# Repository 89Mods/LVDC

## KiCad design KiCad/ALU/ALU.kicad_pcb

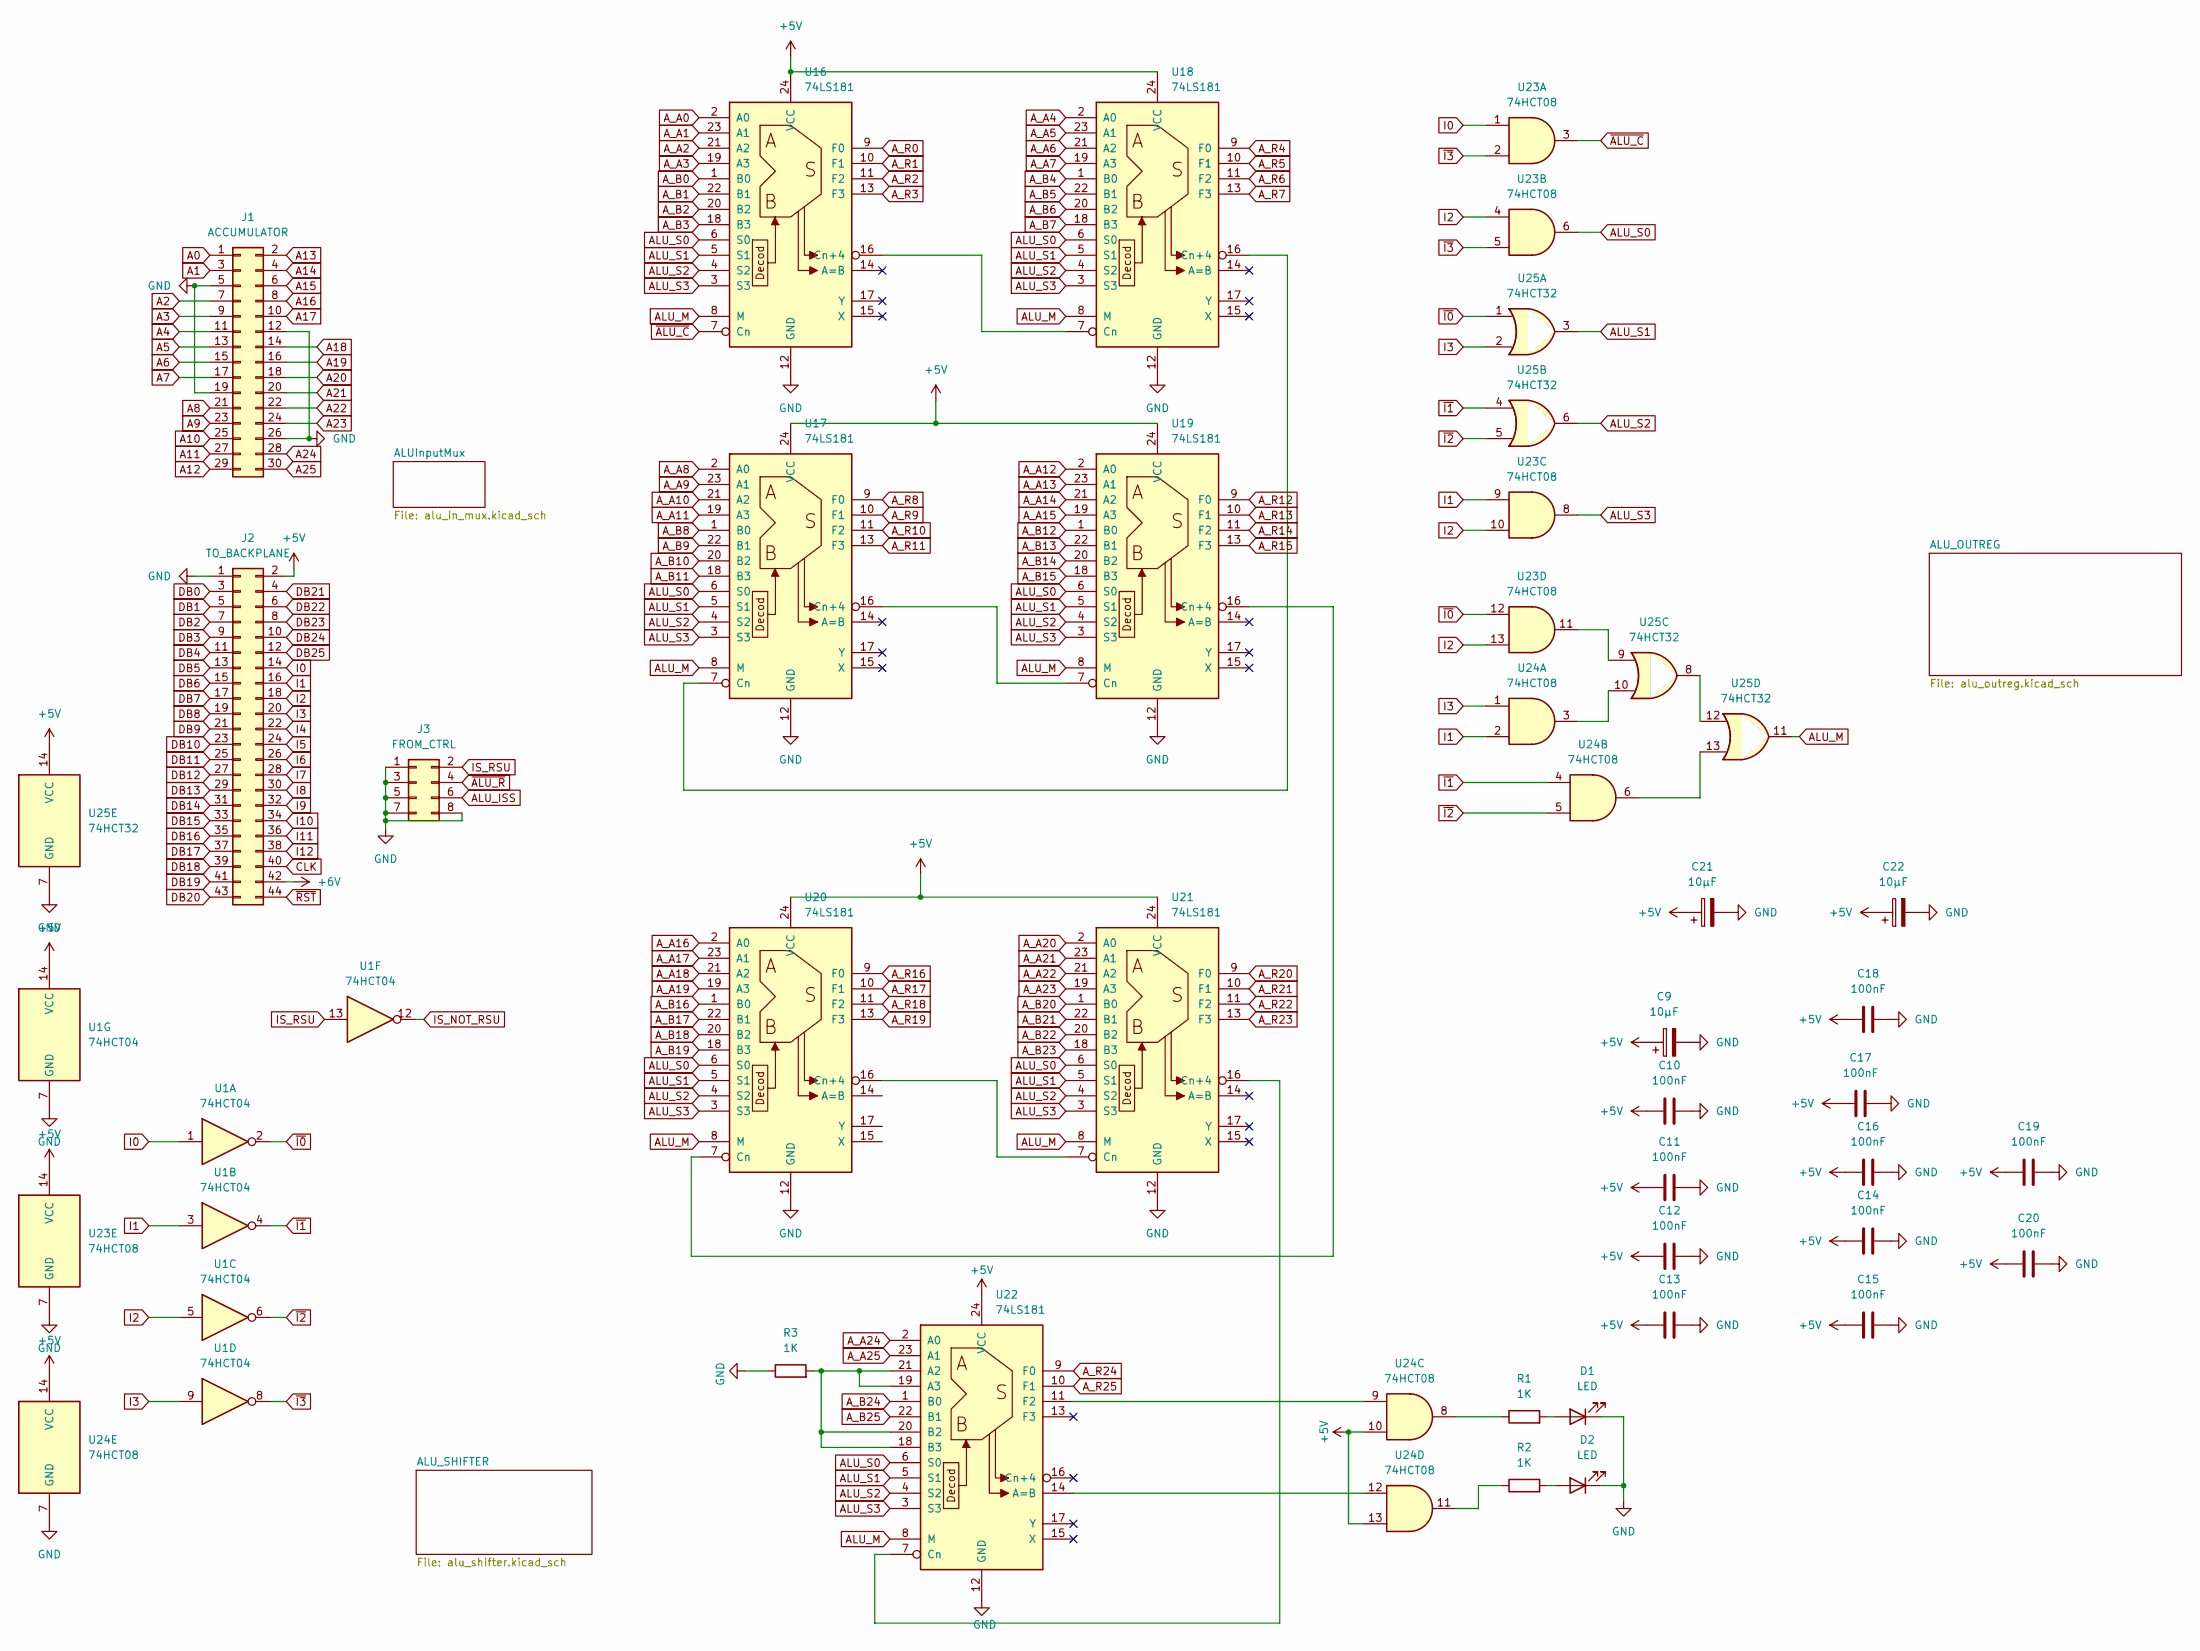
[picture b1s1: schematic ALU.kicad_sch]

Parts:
C9, C21, C22: 10µF; CP_Radial_D4.0mm_P2.00mm
C10, C11, C12, C13, C14, C15, C16, C17, C18, C19, C20: 100nF; C_0805_2012Metric_Pad1.18x1.45mm_HandSolder
D1, D2: LED; LED_1206_3216Metric_Pad1.42x1.75mm_HandSolder
J1: ACCUMULATOR; PinHeader_2x15_P2.54mm_Vertical
J2: TO_BACKPLANE; PinHeader_2x22_P2.54mm_Vertical
J3: FROM_CTRL; PinHeader_2x04_P2.54mm_Vertical
R1, R2, R3: 1K; R_1206_3216Metric_Pad1.30x1.75mm_HandSolder
U1: 74HCT04; SO-14_3.9x8.65mm_P1.27mm
U16, U17, U18, U19, U20, U21, U22: 74LS181; DIP-24_W15.24mm
U23, U24: 74HCT08; SO-14_3.9x8.65mm_P1.27mm
U25: 74HCT32; SO-14_3.9x8.65mm_P1.27mm

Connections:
+5V: C9.1, C10.1, C11.1, C12.1, C13.1, C14.1, C15.1, C16.1, C17.1, C18.1, C19.1, C20.1, C21.1, C22.1, J2.2, U1.14 (VCC), U16.24 (VCC), U17.24 (VCC), U18.24 (VCC), U19.24 (VCC), U20.24 (VCC), U21.24 (VCC), U22.24 (VCC), U23.14 (VCC), U24.10, U24.13, U24.14 (VCC), U25.14 (VCC); also elsewhere on the board
+6V: J2.42; also elsewhere on the board
A0: J1.1; also elsewhere on the board
A1: J1.3; also elsewhere on the board
A2: J1.7; also elsewhere on the board
A3: J1.9; also elsewhere on the board
A4: J1.11; also elsewhere on the board
A5: J1.13; also elsewhere on the board
A6: J1.15; also elsewhere on the board
A7: J1.17; also elsewhere on the board
A8: J1.21; also elsewhere on the board
A9: J1.23; also elsewhere on the board
A10: J1.25; also elsewhere on the board
A11: J1.27; also elsewhere on the board
A12: J1.29; also elsewhere on the board
A13: J1.2; also elsewhere on the board
A14: J1.4; also elsewhere on the board
A15: J1.6; also elsewhere on the board
A16: J1.8; also elsewhere on the board
A17: J1.10; also elsewhere on the board
A18: J1.14; also elsewhere on the board
A19: J1.16; also elsewhere on the board
A20: J1.18; also elsewhere on the board
A21: J1.20; also elsewhere on the board
A22: J1.22; also elsewhere on the board
A23: J1.24; also elsewhere on the board
A24: J1.28; also elsewhere on the board
A25: J1.30; also elsewhere on the board
ALU_ISS: J3.6; also elsewhere on the board
ALU_M: U16.8 (M), U17.8 (M), U18.8 (M), U19.8 (M), U20.8 (M), U21.8 (M), U22.8 (M), U25.11
ALU_S0: U16.6 (S0), U17.6 (S0), U18.6 (S0), U19.6 (S0), U20.6 (S0), U21.6 (S0), U22.6 (S0), U23.6
ALU_S1: U16.5 (S1), U17.5 (S1), U18.5 (S1), U19.5 (S1), U20.5 (S1), U21.5 (S1), U22.5 (S1), U25.3
ALU_S2: U16.4 (S2), U17.4 (S2), U18.4 (S2), U19.4 (S2), U20.4 (S2), U21.4 (S2), U22.4 (S2), U25.6
ALU_S3: U16.3 (S3), U17.3 (S3), U18.3 (S3), U19.3 (S3), U20.3 (S3), U21.3 (S3), U22.3 (S3), U23.8
A_A0: U16.2 (A0); also elsewhere on the board
A_A1: U16.23 (A1); also elsewhere on the board
A_A2: U16.21 (A2); also elsewhere on the board
A_A3: U16.19 (A3); also elsewhere on the board
A_A4: U18.2 (A0); also elsewhere on the board
A_A5: U18.23 (A1); also elsewhere on the board
A_A6: U18.21 (A2); also elsewhere on the board
A_A7: U18.19 (A3); also elsewhere on the board
A_A8: U17.2 (A0); also elsewhere on the board
A_A9: U17.23 (A1); also elsewhere on the board
A_A10: U17.21 (A2); also elsewhere on the board
A_A11: U17.19 (A3); also elsewhere on the board
A_A12: U19.2 (A0); also elsewhere on the board
A_A13: U19.23 (A1); also elsewhere on the board
A_A14: U19.21 (A2); also elsewhere on the board
A_A15: U19.19 (A3); also elsewhere on the board
A_A16: U20.2 (A0); also elsewhere on the board
A_A17: U20.23 (A1); also elsewhere on the board
A_A18: U20.21 (A2); also elsewhere on the board
A_A19: U20.19 (A3); also elsewhere on the board
A_A20: U21.2 (A0); also elsewhere on the board
A_A21: U21.23 (A1); also elsewhere on the board
A_A22: U21.21 (A2); also elsewhere on the board
A_A23: U21.19 (A3); also elsewhere on the board
A_A24: U22.2 (A0); also elsewhere on the board
A_A25: U22.23 (A1); also elsewhere on the board
A_B0: U16.1 (B0); also elsewhere on the board
A_B1: U16.22 (B1); also elsewhere on the board
A_B2: U16.20 (B2); also elsewhere on the board
A_B3: U16.18 (B3); also elsewhere on the board
A_B4: U18.1 (B0); also elsewhere on the board
A_B5: U18.22 (B1); also elsewhere on the board
A_B6: U18.20 (B2); also elsewhere on the board
A_B7: U18.18 (B3); also elsewhere on the board
A_B8: U17.1 (B0); also elsewhere on the board
A_B9: U17.22 (B1); also elsewhere on the board
A_B10: U17.20 (B2); also elsewhere on the board
A_B11: U17.18 (B3); also elsewhere on the board
A_B12: U19.1 (B0); also elsewhere on the board
A_B13: U19.22 (B1); also elsewhere on the board
A_B14: U19.20 (B2); also elsewhere on the board
A_B15: U19.18 (B3); also elsewhere on the board
A_B16: U20.1 (B0); also elsewhere on the board
A_B17: U20.22 (B1); also elsewhere on the board
A_B18: U20.20 (B2); also elsewhere on the board
A_B19: U20.18 (B3); also elsewhere on the board
A_B20: U21.1 (B0); also elsewhere on the board
A_B21: U21.22 (B1); also elsewhere on the board
A_B22: U21.20 (B2); also elsewhere on the board
A_B23: U21.18 (B3); also elsewhere on the board
A_B24: U22.1 (B0); also elsewhere on the board
A_B25: U22.22 (B1); also elsewhere on the board
A_R0: U16.9 (F0); also elsewhere on the board
A_R1: U16.10 (F1); also elsewhere on the board
A_R2: U16.11 (F2); also elsewhere on the board
A_R3: U16.13 (F3); also elsewhere on the board
A_R4: U18.9 (F0); also elsewhere on the board
A_R5: U18.10 (F1); also elsewhere on the board
A_R6: U18.11 (F2); also elsewhere on the board
A_R7: U18.13 (F3); also elsewhere on the board
A_R8: U17.9 (F0); also elsewhere on the board
A_R9: U17.10 (F1); also elsewhere on the board
A_R10: U17.11 (F2); also elsewhere on the board
A_R11: U17.13 (F3); also elsewhere on the board
A_R12: U19.9 (F0); also elsewhere on the board
A_R13: U19.10 (F1); also elsewhere on the board
A_R14: U19.11 (F2); also elsewhere on the board
A_R15: U19.13 (F3); also elsewhere on the board
A_R16: U20.9 (F0); also elsewhere on the board
A_R17: U20.10 (F1); also elsewhere on the board
A_R18: U20.11 (F2); also elsewhere on the board
A_R19: U20.13 (F3); also elsewhere on the board
A_R20: U21.9 (F0); also elsewhere on the board
A_R21: U21.10 (F1); also elsewhere on the board
A_R22: U21.11 (F2); also elsewhere on the board
A_R23: U21.13 (F3); also elsewhere on the board
A_R24: U22.9 (F0); also elsewhere on the board
A_R25: U22.10 (F1); also elsewhere on the board
CLK: J2.40; also elsewhere on the board
DB0: J2.3; also elsewhere on the board
DB1: J2.5; also elsewhere on the board
DB2: J2.7; also elsewhere on the board
DB3: J2.9; also elsewhere on the board
DB4: J2.11; also elsewhere on the board
DB5: J2.13; also elsewhere on the board
DB6: J2.15; also elsewhere on the board
DB7: J2.17; also elsewhere on the board
DB8: J2.19; also elsewhere on the board
DB9: J2.21; also elsewhere on the board
DB10: J2.23; also elsewhere on the board
DB11: J2.25; also elsewhere on the board
DB12: J2.27; also elsewhere on the board
DB13: J2.29; also elsewhere on the board
DB14: J2.31; also elsewhere on the board
DB15: J2.33; also elsewhere on the board
DB16: J2.35; also elsewhere on the board
DB17: J2.37; also elsewhere on the board
DB18: J2.39; also elsewhere on the board
DB19: J2.41; also elsewhere on the board
DB20: J2.43; also elsewhere on the board
DB21: J2.4; also elsewhere on the board
DB22: J2.6; also elsewhere on the board
DB23: J2.8; also elsewhere on the board
DB24: J2.10; also elsewhere on the board
DB25: J2.12; also elsewhere on the board
GND: C9.2, C10.2, C11.2, C12.2, C13.2, C14.2, C15.2, C16.2, C17.2, C18.2, C19.2, C20.2, C21.2, C22.2, D1.1 (K), D2.1 (K), J1.5, J1.12, J1.19, J1.26, J2.1, J3.1, J3.3, J3.5, J3.7, J3.8, R3.1, U1.7 (GND), U16.12 (GND), U17.12 (GND), U18.12 (GND), U19.12 (GND), U20.12 (GND), U21.12 (GND), U22.12 (GND), U23.7 (GND), U24.7 (GND), U25.7 (GND); also elsewhere on the board
I0: J2.14, U1.1, U23.1
I1: J2.16, U1.3, U23.9, U24.2
I2: J2.18, U1.5, U23.4, U23.10, U23.13
I3: J2.20, U1.9, U24.1, U25.2
I4: J2.22
I5: J2.24; also elsewhere on the board
I6: J2.26; also elsewhere on the board
I7: J2.28
I8: J2.30
I9: J2.32; also elsewhere on the board
I10: J2.34; also elsewhere on the board
I11: J2.36
I12: J2.38
IS_NOT_RSU: U1.12; also elsewhere on the board
IS_RSU: J3.2, U1.13; also elsewhere on the board
unnamed: D1.2 (A), R1.2
unnamed: D2.2 (A), R2.2
unnamed: R1.1, U24.8
unnamed: R2.1, U24.11
unnamed: U16.16 (Cn+4), U18.7 (Cn)
unnamed: U17.7 (Cn), U18.16 (Cn+4)
unnamed: U17.16 (Cn+4), U19.7 (Cn)
unnamed: U19.16 (Cn+4), U20.7 (Cn)
unnamed: U20.16 (Cn+4), U21.7 (Cn)
unnamed: U21.16 (Cn+4), U22.7 (Cn)
unnamed: R3.2, U22.18 (B3), U22.19 (A3), U22.20 (B2), U22.21 (A2)
unnamed: U22.14 (A=B), U24.12
unnamed: U22.11 (F2), U24.9
unnamed: U23.11, U25.9
unnamed: U24.3, U25.10
unnamed: U24.6, U25.13
unnamed: U25.8, U25.12
~ALU_C: U16.7 (Cn), U23.3
~ALU_R: J3.4; also elsewhere on the board
~I0: U1.2, U23.12, U25.1
~I1: U1.4, U24.4, U25.4
~I2: U1.6, U24.5, U25.5
~I3: U1.8, U23.2, U23.5
~RST: J2.44

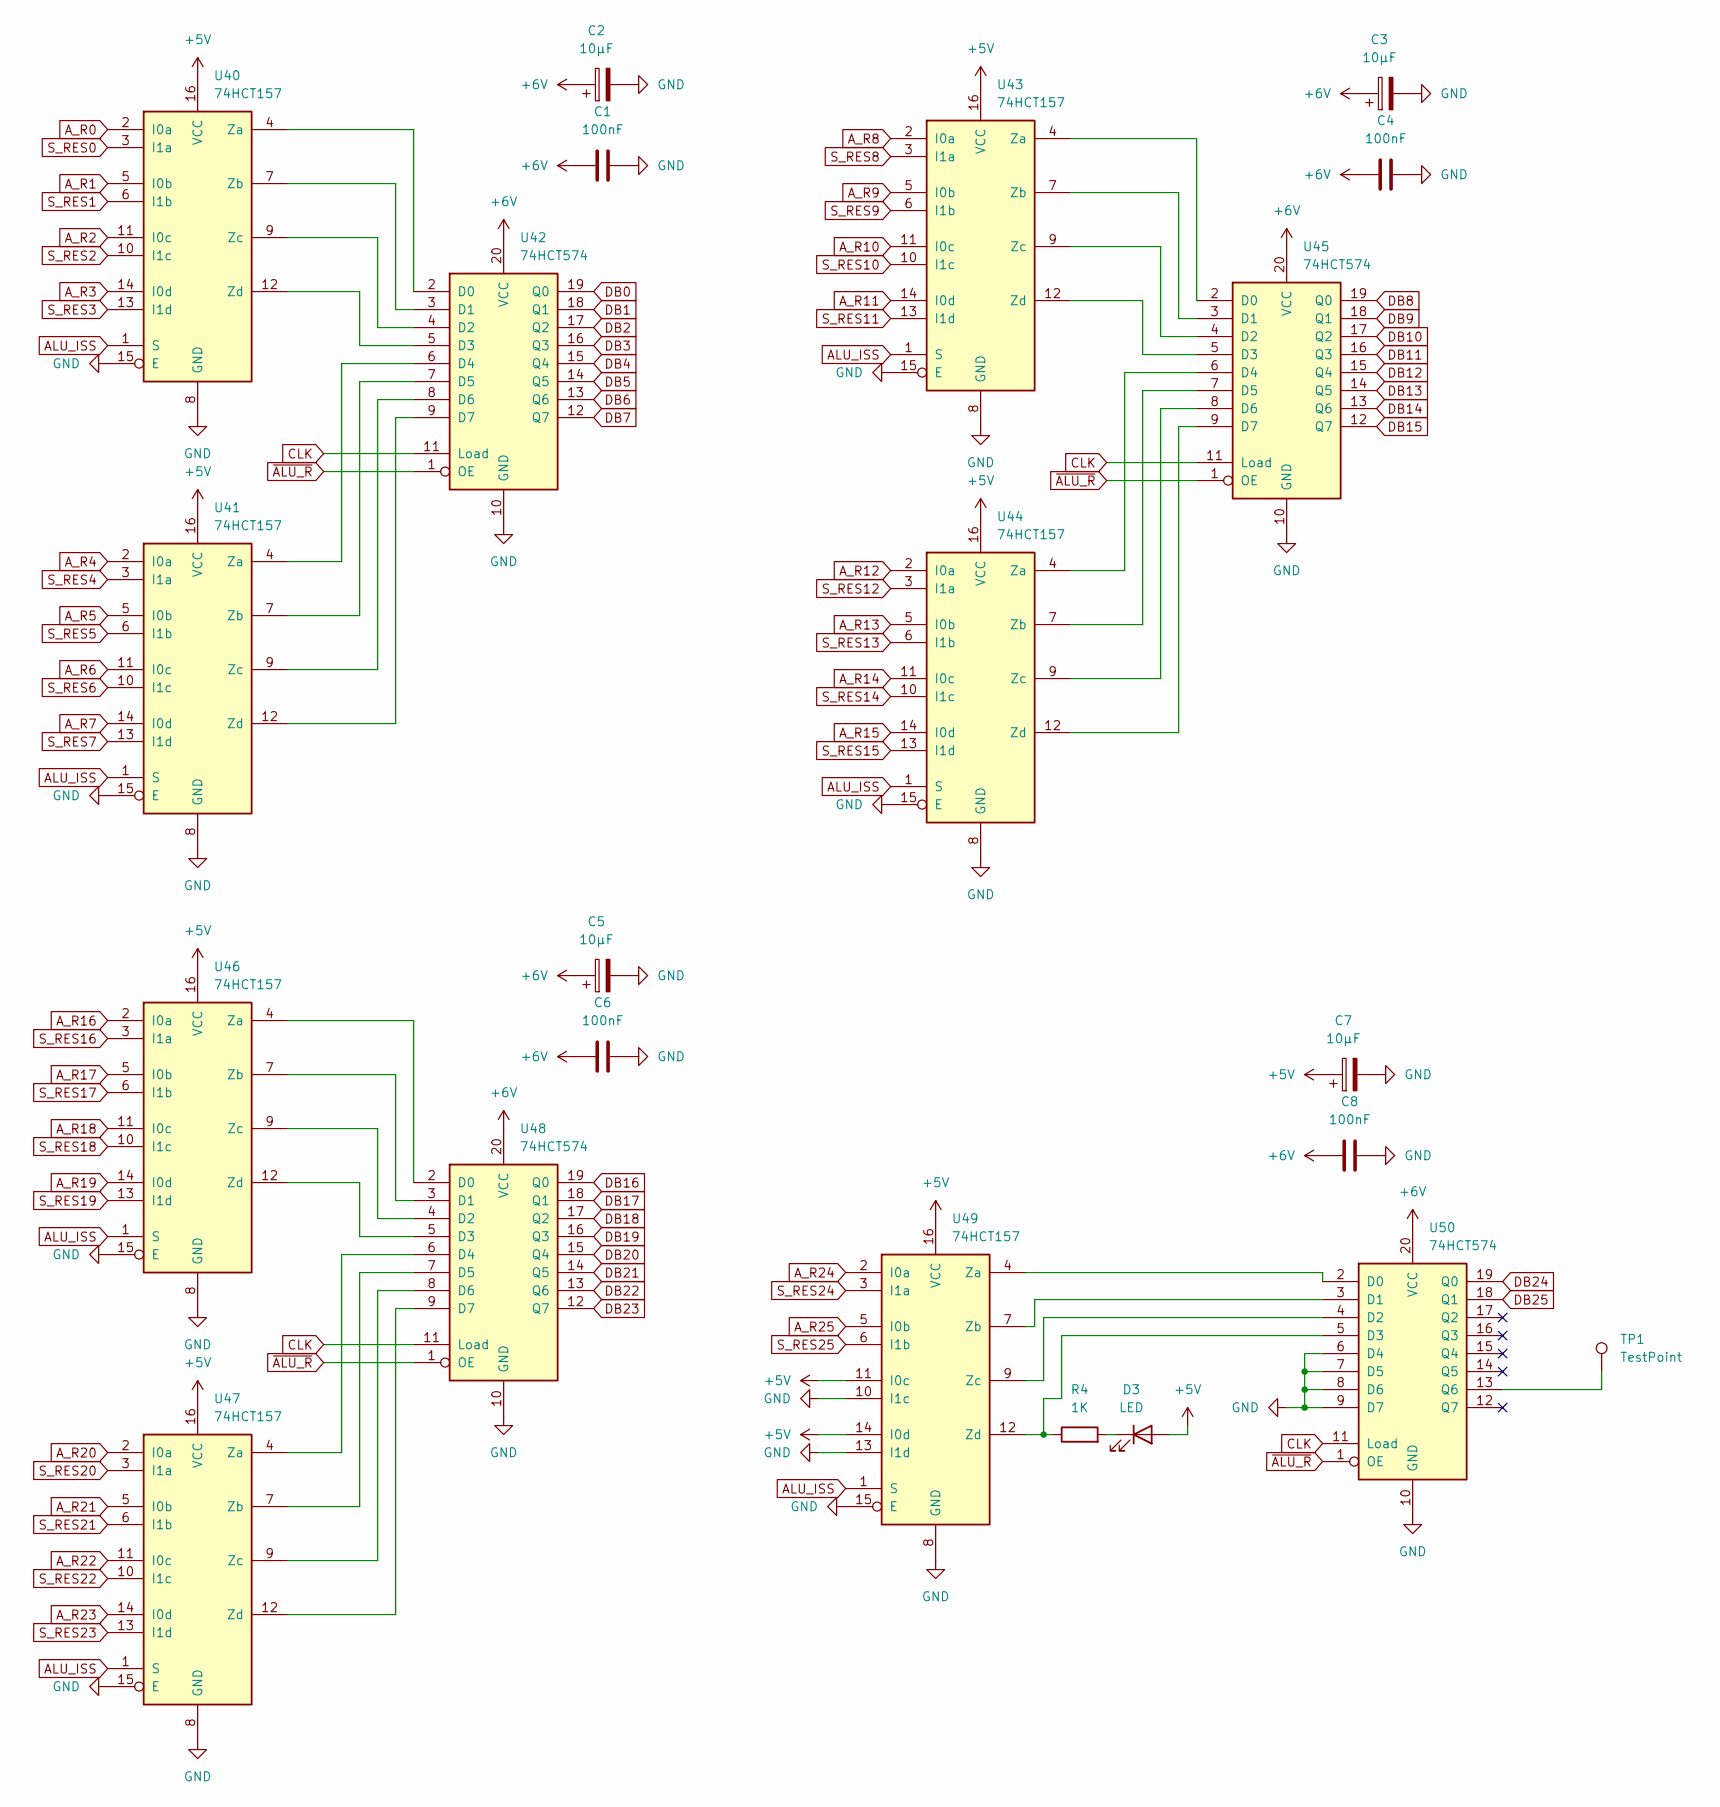
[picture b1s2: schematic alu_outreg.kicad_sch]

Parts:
C1, C4, C6, C8: 100nF; C_0805_2012Metric_Pad1.18x1.45mm_HandSolder
C2, C3, C5, C7: 10µF; CP_Radial_D4.0mm_P2.00mm
D3: LED; LED_1206_3216Metric_Pad1.42x1.75mm_HandSolder
R4: 1K; R_1206_3216Metric_Pad1.30x1.75mm_HandSolder
TP1: TestPoint; TestPoint_Pad_1.5x1.5mm
U40, U41, U43, U44, U46, U47, U49: 74HCT157; SO-16_3.9x9.9mm_P1.27mm
U42, U45, U48, U50: 74HCT574; SO-20_12.8x7.5mm_P1.27mm

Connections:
+5V: C7.1, D3.2 (A), U40.16 (VCC), U41.16 (VCC), U43.16 (VCC), U44.16 (VCC), U46.16 (VCC), U47.16 (VCC), U49.11 (I0c), U49.14 (I0d), U49.16 (VCC); also elsewhere on the board
+6V: C1.1, C2.1, C3.1, C4.1, C5.1, C6.1, C8.1, U42.20 (VCC), U45.20 (VCC), U48.20 (VCC), U50.20 (VCC); also elsewhere on the board
ALU_ISS: U40.1 (S), U41.1 (S), U43.1 (S), U44.1 (S), U46.1 (S), U47.1 (S), U49.1 (S); also elsewhere on the board
A_R0: U40.2 (I0a); also elsewhere on the board
A_R1: U40.5 (I0b); also elsewhere on the board
A_R2: U40.11 (I0c); also elsewhere on the board
A_R3: U40.14 (I0d); also elsewhere on the board
A_R4: U41.2 (I0a); also elsewhere on the board
A_R5: U41.5 (I0b); also elsewhere on the board
A_R6: U41.11 (I0c); also elsewhere on the board
A_R7: U41.14 (I0d); also elsewhere on the board
A_R8: U43.2 (I0a); also elsewhere on the board
A_R9: U43.5 (I0b); also elsewhere on the board
A_R10: U43.11 (I0c); also elsewhere on the board
A_R11: U43.14 (I0d); also elsewhere on the board
A_R12: U44.2 (I0a); also elsewhere on the board
A_R13: U44.5 (I0b); also elsewhere on the board
A_R14: U44.11 (I0c); also elsewhere on the board
A_R15: U44.14 (I0d); also elsewhere on the board
A_R16: U46.2 (I0a); also elsewhere on the board
A_R17: U46.5 (I0b); also elsewhere on the board
A_R18: U46.11 (I0c); also elsewhere on the board
A_R19: U46.14 (I0d); also elsewhere on the board
A_R20: U47.2 (I0a); also elsewhere on the board
A_R21: U47.5 (I0b); also elsewhere on the board
A_R22: U47.11 (I0c); also elsewhere on the board
A_R23: U47.14 (I0d); also elsewhere on the board
A_R24: U49.2 (I0a); also elsewhere on the board
A_R25: U49.5 (I0b); also elsewhere on the board
CLK: U42.11 (Load), U45.11 (Load), U48.11 (Load), U50.11 (Load); also elsewhere on the board
DB0: U42.19 (Q0); also elsewhere on the board
DB1: U42.18 (Q1); also elsewhere on the board
DB2: U42.17 (Q2); also elsewhere on the board
DB3: U42.16 (Q3); also elsewhere on the board
DB4: U42.15 (Q4); also elsewhere on the board
DB5: U42.14 (Q5); also elsewhere on the board
DB6: U42.13 (Q6); also elsewhere on the board
DB7: U42.12 (Q7); also elsewhere on the board
DB8: U45.19 (Q0); also elsewhere on the board
DB9: U45.18 (Q1); also elsewhere on the board
DB10: U45.17 (Q2); also elsewhere on the board
DB11: U45.16 (Q3); also elsewhere on the board
DB12: U45.15 (Q4); also elsewhere on the board
DB13: U45.14 (Q5); also elsewhere on the board
DB14: U45.13 (Q6); also elsewhere on the board
DB15: U45.12 (Q7); also elsewhere on the board
DB16: U48.19 (Q0); also elsewhere on the board
DB17: U48.18 (Q1); also elsewhere on the board
DB18: U48.17 (Q2); also elsewhere on the board
DB19: U48.16 (Q3); also elsewhere on the board
DB20: U48.15 (Q4); also elsewhere on the board
DB21: U48.14 (Q5); also elsewhere on the board
DB22: U48.13 (Q6); also elsewhere on the board
DB23: U48.12 (Q7); also elsewhere on the board
DB24: U50.19 (Q0); also elsewhere on the board
DB25: U50.18 (Q1); also elsewhere on the board
GND: C1.2, C2.2, C3.2, C4.2, C5.2, C6.2, C7.2, C8.2, U40.8 (GND), U40.15 (E), U41.8 (GND), U41.15 (E), U42.10 (GND), U43.8 (GND), U43.15 (E), U44.8 (GND), U44.15 (E), U45.10 (GND), U46.8 (GND), U46.15 (E), U47.8 (GND), U47.15 (E), U48.10 (GND), U49.8 (GND), U49.10 (I1c), U49.13 (I1d), U49.15 (E), U50.6 (D4), U50.7 (D5), U50.8 (D6), U50.9 (D7), U50.10 (GND); also elsewhere on the board
unnamed: D3.1 (K), R4.2
unnamed: U40.4 (Za), U42.2 (D0)
unnamed: U40.7 (Zb), U42.3 (D1)
unnamed: U40.9 (Zc), U42.4 (D2)
unnamed: U40.12 (Zd), U42.5 (D3)
unnamed: U41.4 (Za), U42.6 (D4)
unnamed: U41.7 (Zb), U42.7 (D5)
unnamed: U41.9 (Zc), U42.8 (D6)
unnamed: U41.12 (Zd), U42.9 (D7)
unnamed: U43.4 (Za), U45.2 (D0)
unnamed: U43.7 (Zb), U45.3 (D1)
unnamed: U43.9 (Zc), U45.4 (D2)
unnamed: U43.12 (Zd), U45.5 (D3)
unnamed: U44.4 (Za), U45.6 (D4)
unnamed: U44.7 (Zb), U45.7 (D5)
unnamed: U44.9 (Zc), U45.8 (D6)
unnamed: U44.12 (Zd), U45.9 (D7)
unnamed: U46.4 (Za), U48.2 (D0)
unnamed: U46.7 (Zb), U48.3 (D1)
unnamed: U46.9 (Zc), U48.4 (D2)
unnamed: U46.12 (Zd), U48.5 (D3)
unnamed: U47.4 (Za), U48.6 (D4)
unnamed: U47.7 (Zb), U48.7 (D5)
unnamed: U47.9 (Zc), U48.8 (D6)
unnamed: U47.12 (Zd), U48.9 (D7)
unnamed: U49.4 (Za), U50.2 (D0)
unnamed: U49.7 (Zb), U50.3 (D1)
unnamed: U49.9 (Zc), U50.4 (D2)
unnamed: R4.1, U49.12 (Zd), U50.5 (D3)
unnamed: TP1.1, U50.13 (Q6)
S_RES0: U40.3 (I1a); also elsewhere on the board
S_RES1: U40.6 (I1b); also elsewhere on the board
S_RES2: U40.10 (I1c); also elsewhere on the board
S_RES3: U40.13 (I1d); also elsewhere on the board
S_RES4: U41.3 (I1a); also elsewhere on the board
S_RES5: U41.6 (I1b); also elsewhere on the board
S_RES6: U41.10 (I1c); also elsewhere on the board
S_RES7: U41.13 (I1d); also elsewhere on the board
S_RES8: U43.3 (I1a); also elsewhere on the board
S_RES9: U43.6 (I1b); also elsewhere on the board
S_RES10: U43.10 (I1c); also elsewhere on the board
S_RES11: U43.13 (I1d); also elsewhere on the board
S_RES12: U44.3 (I1a); also elsewhere on the board
S_RES13: U44.6 (I1b); also elsewhere on the board
S_RES14: U44.10 (I1c); also elsewhere on the board
S_RES15: U44.13 (I1d); also elsewhere on the board
S_RES16: U46.3 (I1a); also elsewhere on the board
S_RES17: U46.6 (I1b); also elsewhere on the board
S_RES18: U46.10 (I1c); also elsewhere on the board
S_RES19: U46.13 (I1d); also elsewhere on the board
S_RES20: U47.3 (I1a); also elsewhere on the board
S_RES21: U47.6 (I1b); also elsewhere on the board
S_RES22: U47.10 (I1c); also elsewhere on the board
S_RES23: U47.13 (I1d); also elsewhere on the board
S_RES24: U49.3 (I1a); also elsewhere on the board
S_RES25: U49.6 (I1b); also elsewhere on the board
~ALU_R: U42.1 (OE), U45.1 (OE), U48.1 (OE), U50.1 (OE); also elsewhere on the board

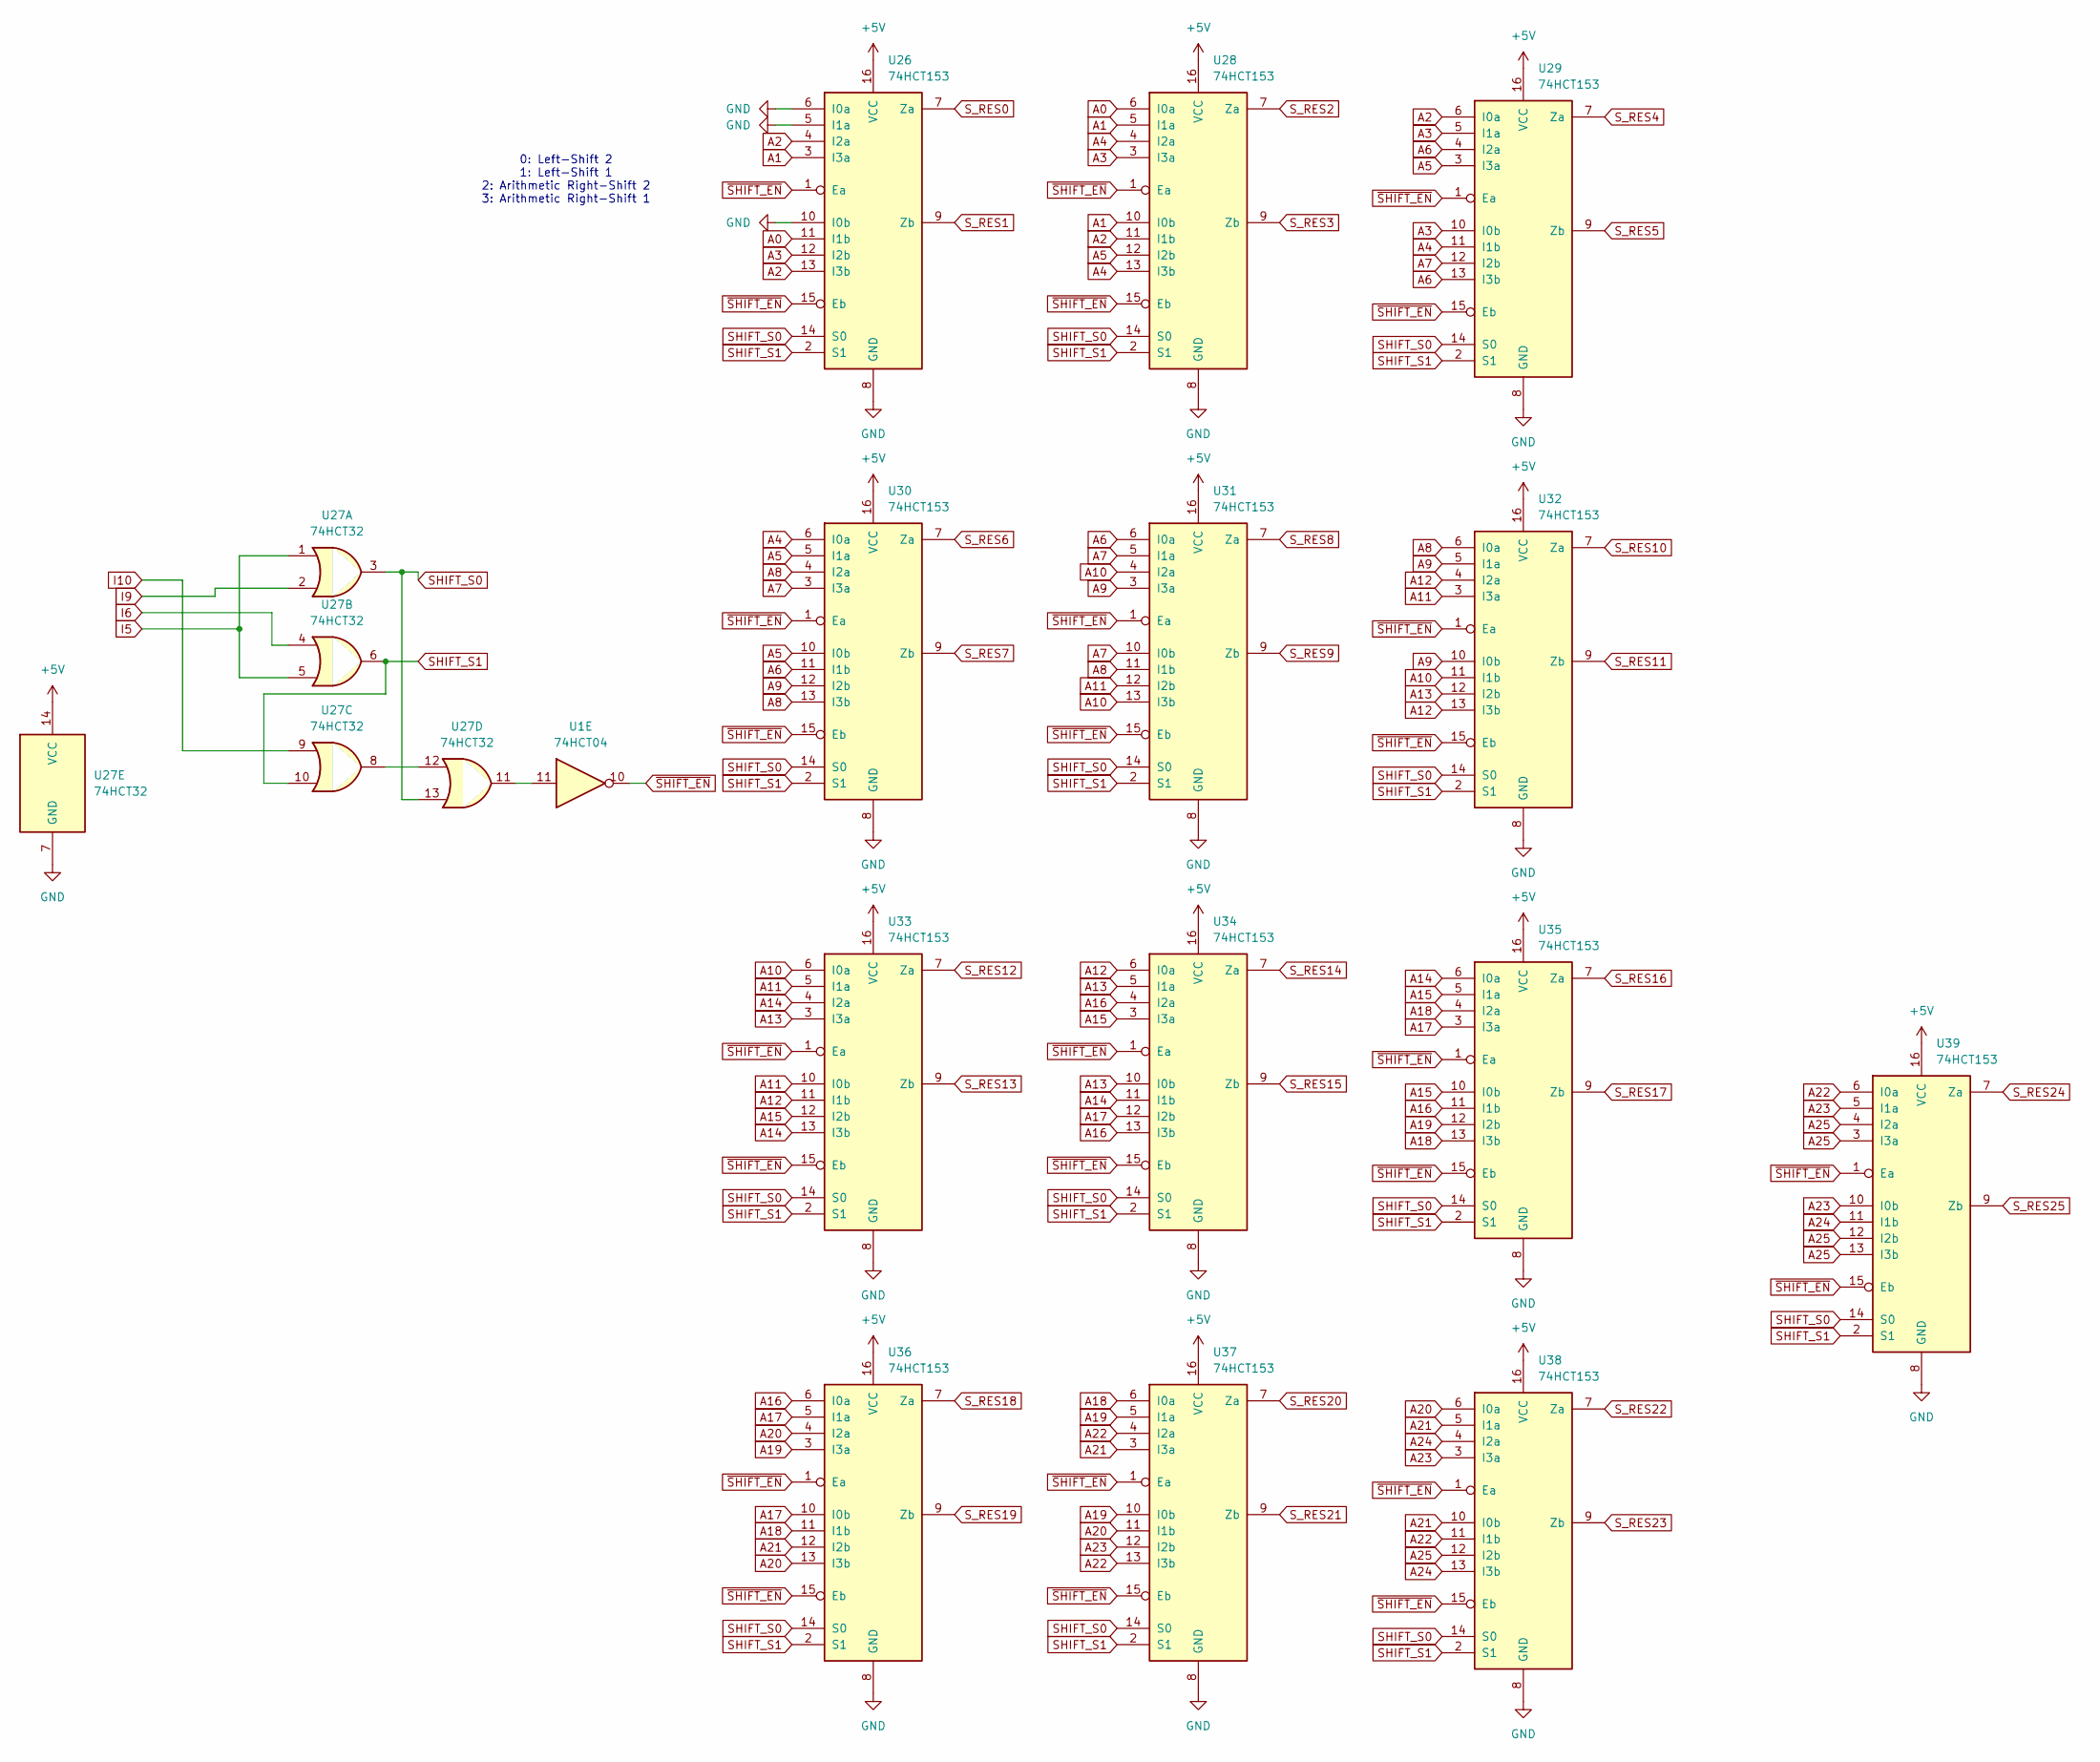
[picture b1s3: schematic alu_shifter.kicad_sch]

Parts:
U1: 74HCT04; SO-14_3.9x8.65mm_P1.27mm
U26, U28, U29, U30, U31, U32, U33, U34, U35, U36, U37, U38, U39: 74HCT153; SO-16_3.9x9.9mm_P1.27mm
U27: 74HCT32; SO-14_3.9x8.65mm_P1.27mm

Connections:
+5V: U26.16 (VCC), U27.14 (VCC), U28.16 (VCC), U29.16 (VCC), U30.16 (VCC), U31.16 (VCC), U32.16 (VCC), U33.16 (VCC), U34.16 (VCC), U35.16 (VCC), U36.16 (VCC), U37.16 (VCC), U38.16 (VCC), U39.16 (VCC); also elsewhere on the board
A0: U26.11 (I1b), U28.6 (I0a); also elsewhere on the board
A1: U26.3 (I3a), U28.5 (I1a), U28.10 (I0b); also elsewhere on the board
A2: U26.4 (I2a), U26.13 (I3b), U28.11 (I1b), U29.6 (I0a); also elsewhere on the board
A3: U26.12 (I2b), U28.3 (I3a), U29.5 (I1a), U29.10 (I0b); also elsewhere on the board
A4: U28.4 (I2a), U28.13 (I3b), U29.11 (I1b), U30.6 (I0a); also elsewhere on the board
A5: U28.12 (I2b), U29.3 (I3a), U30.5 (I1a), U30.10 (I0b); also elsewhere on the board
A6: U29.4 (I2a), U29.13 (I3b), U30.11 (I1b), U31.6 (I0a); also elsewhere on the board
A7: U29.12 (I2b), U30.3 (I3a), U31.5 (I1a), U31.10 (I0b); also elsewhere on the board
A8: U30.4 (I2a), U30.13 (I3b), U31.11 (I1b), U32.6 (I0a); also elsewhere on the board
A9: U30.12 (I2b), U31.3 (I3a), U32.5 (I1a), U32.10 (I0b); also elsewhere on the board
A10: U31.4 (I2a), U31.13 (I3b), U32.11 (I1b), U33.6 (I0a); also elsewhere on the board
A11: U31.12 (I2b), U32.3 (I3a), U33.5 (I1a), U33.10 (I0b); also elsewhere on the board
A12: U32.4 (I2a), U32.13 (I3b), U33.11 (I1b), U34.6 (I0a); also elsewhere on the board
A13: U32.12 (I2b), U33.3 (I3a), U34.5 (I1a), U34.10 (I0b); also elsewhere on the board
A14: U33.4 (I2a), U33.13 (I3b), U34.11 (I1b), U35.6 (I0a); also elsewhere on the board
A15: U33.12 (I2b), U34.3 (I3a), U35.5 (I1a), U35.10 (I0b); also elsewhere on the board
A16: U34.4 (I2a), U34.13 (I3b), U35.11 (I1b), U36.6 (I0a); also elsewhere on the board
A17: U34.12 (I2b), U35.3 (I3a), U36.5 (I1a), U36.10 (I0b); also elsewhere on the board
A18: U35.4 (I2a), U35.13 (I3b), U36.11 (I1b), U37.6 (I0a); also elsewhere on the board
A19: U35.12 (I2b), U36.3 (I3a), U37.5 (I1a), U37.10 (I0b); also elsewhere on the board
A20: U36.4 (I2a), U36.13 (I3b), U37.11 (I1b), U38.6 (I0a); also elsewhere on the board
A21: U36.12 (I2b), U37.3 (I3a), U38.5 (I1a), U38.10 (I0b); also elsewhere on the board
A22: U37.4 (I2a), U37.13 (I3b), U38.11 (I1b), U39.6 (I0a); also elsewhere on the board
A23: U37.12 (I2b), U38.3 (I3a), U39.5 (I1a), U39.10 (I0b); also elsewhere on the board
A24: U38.4 (I2a), U38.13 (I3b), U39.11 (I1b); also elsewhere on the board
A25: U38.12 (I2b), U39.3 (I3a), U39.4 (I2a), U39.12 (I2b), U39.13 (I3b); also elsewhere on the board
GND: U26.5 (I1a), U26.6 (I0a), U26.8 (GND), U26.10 (I0b), U27.7 (GND), U28.8 (GND), U29.8 (GND), U30.8 (GND), U31.8 (GND), U32.8 (GND), U33.8 (GND), U34.8 (GND), U35.8 (GND), U36.8 (GND), U37.8 (GND), U38.8 (GND), U39.8 (GND); also elsewhere on the board
I5: U27.1, U27.5; also elsewhere on the board
I6: U27.4; also elsewhere on the board
I9: U27.2; also elsewhere on the board
I10: U27.9; also elsewhere on the board
unnamed: U1.11, U27.11
unnamed: U27.8, U27.12
SHIFT_S0: U26.14 (S0), U27.3, U27.13, U28.14 (S0), U29.14 (S0), U30.14 (S0), U31.14 (S0), U32.14 (S0), U33.14 (S0), U34.14 (S0), U35.14 (S0), U36.14 (S0), U37.14 (S0), U38.14 (S0), U39.14 (S0)
SHIFT_S1: U26.2 (S1), U27.6, U27.10, U28.2 (S1), U29.2 (S1), U30.2 (S1), U31.2 (S1), U32.2 (S1), U33.2 (S1), U34.2 (S1), U35.2 (S1), U36.2 (S1), U37.2 (S1), U38.2 (S1), U39.2 (S1)
S_RES0: U26.7 (Za); also elsewhere on the board
S_RES1: U26.9 (Zb); also elsewhere on the board
S_RES2: U28.7 (Za); also elsewhere on the board
S_RES3: U28.9 (Zb); also elsewhere on the board
S_RES4: U29.7 (Za); also elsewhere on the board
S_RES5: U29.9 (Zb); also elsewhere on the board
S_RES6: U30.7 (Za); also elsewhere on the board
S_RES7: U30.9 (Zb); also elsewhere on the board
S_RES8: U31.7 (Za); also elsewhere on the board
S_RES9: U31.9 (Zb); also elsewhere on the board
S_RES10: U32.7 (Za); also elsewhere on the board
S_RES11: U32.9 (Zb); also elsewhere on the board
S_RES12: U33.7 (Za); also elsewhere on the board
S_RES13: U33.9 (Zb); also elsewhere on the board
S_RES14: U34.7 (Za); also elsewhere on the board
S_RES15: U34.9 (Zb); also elsewhere on the board
S_RES16: U35.7 (Za); also elsewhere on the board
S_RES17: U35.9 (Zb); also elsewhere on the board
S_RES18: U36.7 (Za); also elsewhere on the board
S_RES19: U36.9 (Zb); also elsewhere on the board
S_RES20: U37.7 (Za); also elsewhere on the board
S_RES21: U37.9 (Zb); also elsewhere on the board
S_RES22: U38.7 (Za); also elsewhere on the board
S_RES23: U38.9 (Zb); also elsewhere on the board
S_RES24: U39.7 (Za); also elsewhere on the board
S_RES25: U39.9 (Zb); also elsewhere on the board
~SHIFT_EN: U1.10, U26.1 (Ea), U26.15 (Eb), U28.1 (Ea), U28.15 (Eb), U29.1 (Ea), U29.15 (Eb), U30.1 (Ea), U30.15 (Eb), U31.1 (Ea), U31.15 (Eb), U32.1 (Ea), U32.15 (Eb), U33.1 (Ea), U33.15 (Eb), U34.1 (Ea), U34.15 (Eb), U35.1 (Ea), U35.15 (Eb), U36.1 (Ea), U36.15 (Eb), U37.1 (Ea), U37.15 (Eb), U38.1 (Ea), U38.15 (Eb), U39.1 (Ea), U39.15 (Eb)

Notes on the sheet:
0: Left-Shift 2 1: Left-Shift 1 2: Arithmetic Right-Shift 2 3: Arithmetic Right-Shift 1
